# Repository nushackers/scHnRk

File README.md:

# scHnRk

The scHnRk (pronounced as snark) is a digispark/arduino compatible prototyping board developed for Hack&Roll'16.

The hardware design, firmware and software are derived from Galvant/usb_wrapper-pcb, digispark, micronucleus and arduino. Any derivative from their work is released under the Creative Commons License CC BY 4.0 wherever possible. (I'm no lawyer)

## Hardware

This design is adapted from the venerable DigiSpark.

Here's the lowdown on the stats
- ATTINY85
  - 8KB Flash Memory
  - 512B EEPROM
  - 6 I/O Pins (SPI)
- Acessories
  - 5 WS2812B LEDs
  - 2 CR2032 Battery Holders
  - 2 LEDs (Status, Pwr)
  - USB Wrapper (In some circles its called USB Condom)
  - USB Connector

The scHnRk consists of 2 independent components, separable from one another. The main componenet is a digispark clone which is fully assembled, the smaller component is a partially assembled/ unassembled usb-wrapper-pcb kit. 

## Kits

### Green (unassembled usb-wrapper-pcb)

- Resistor Information for green kits can be inferred from the following  
  - Galvant/usb_wrapper-pcb (Github)
    - Most basic configuration => R7 == 75K Ohm, R9 == 43.2K Ohm, R8 == R10 == 49.9K Ohm
    - R4 == 180 Ohm, LED == LED

### Orange (partially assembled usb-wrapper-pcb)

- Just solder on USB connector and you're set!

## Firmware

A jig will be provided on the day itself for firmware (bootloader) reprogramming using SPI. 

## Software

Feel free to program your arduino anyway you want during the competition using arduino IDE and the "on board" USB port!

## Designed by

```
NUSHackers and Pals

Chang Chu-Ming
Chinmay Pendharkar
Harish Venkatesan
Kenneth Lim
Vishnu Prem
Rahul Gokul
Sayanee Basu
Shanmugam Mpl
Yeo Kheng Meng
Jeremias Wong
```

## Secret Features

One has to be granted WOC REPUS Previleges before one accesses the secret features/puzzle.

There might be prizes for people who crack the puzzle during the hackathon! Maybe we forgot lol?

## Sponsors
 
### Platinum Sponsor
```
Zalora
```

### Gold Sponsors
```
Garena
Palantir
```

### Silver Sponsors
```
Titansoft
Google
Jane Street
Stripe
```

### Bronze Sponsors
```
Zopim
Carousell
NUS School of Computing
```

We thank the sponsors for making this happen.

Also we're looking out for sponsors for the next hackathon! Please contact us at coreteam@nushackers.org!

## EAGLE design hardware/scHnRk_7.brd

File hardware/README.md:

# Hardware

We highlight here the changes made between revisions

## v0.7

## v0.6

Converted to ATTINY85

## v0.1-v0.5

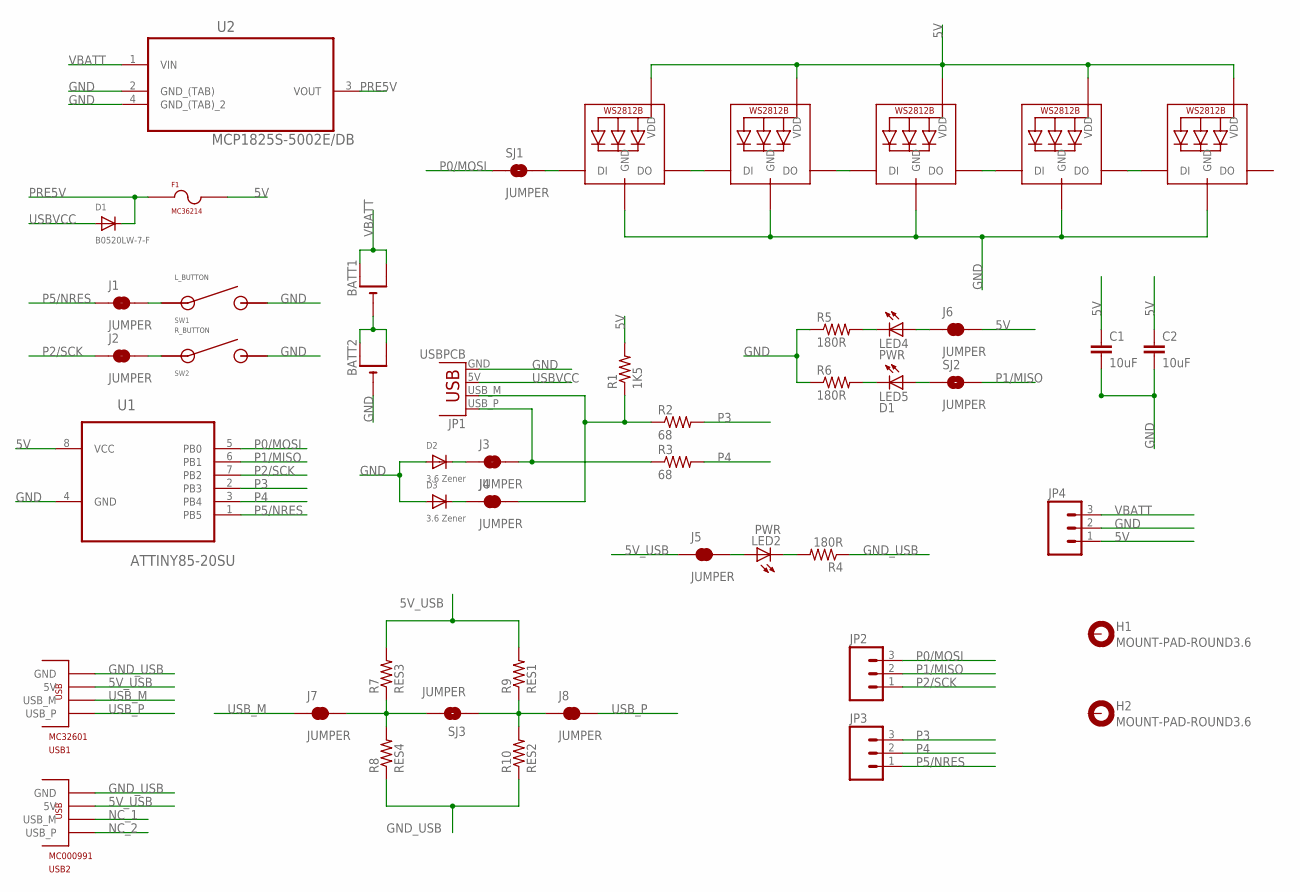
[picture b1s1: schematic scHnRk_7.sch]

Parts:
BATT1, BATT2: CR2032SMT; CR2032-SMD
C1, C2: 10uF; 0805
D1: B0520LW-7-F; SOD-123
D2, D3: 3.6 Zener; SOD-523
F1: MC36214
H1, H2: MOUNT-PAD-ROUND3.6; 3,6-PAD
J1, J2, J3, J4, J5, J6, J7, J8: JUMPER; PAD-JUMPER-2-NC_BY_TRACE_YES_SILK
JP1: USBPCB; USB-A-PCB
JP2, JP3, JP4: M031X03_NO_SILK; 1X03_NO_SILK
LED1, LED3, LED6, LED7, LED8: WS2812B5050; WS2812B
LED2, LED4: PWR; CHIPLED_0603
LED5: D1; CHIPLED_0603
R1: 1K5; 0805
R2, R3: 68; 0805
R4, R5, R6: 180R; 0805
R7: RES3; 0805
R8: RES4; 0805
R9: RES1; 0805
R10: RES2; 0805
SJ1, SJ2, SJ3: JUMPER; PAD-JUMPER-2-NO_YES_SILK
SW1: L_BUTTON; SKRBAGE010
SW2: R_BUTTON; SKRBAGE010
U1: ATTINY85-20SU; SOIC127P798X216-8N
U2: MCP1825S-5002E/DB; SOT230P700X180-4N
USB1: MC32601
USB2: MC000991

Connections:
5V: C1.1, C2.1, F1.P$2, J6.2, JP4.1, LED1.1-VDD (VDD), LED3.1-VDD (VDD), LED6.1-VDD (VDD), LED7.1-VDD (VDD), LED8.1-VDD (VDD), R1.2, U1.8 (VCC)
5V_USB: J5.1, R7.2, R9.2, USB1.P$2 (5V), USB2.P$4 (5V)
GND: BATT2.-, C1.2, C2.2, D2.A, D3.A, JP1.GND, JP4.2, LED1.3-GND (GND), LED3.3-GND (GND), LED6.3-GND (GND), LED7.3-GND (GND), LED8.3-GND (GND), R5.1, R6.1, SW1.P$2, SW1.P$4, SW2.P$2, SW2.P$4, U1.4 (GND), U2.2 (GND_(TAB)), U2.4 (GND_(TAB)_2)
GND_USB: R4.1, R8.1, R10.1, USB1.P$5 (GND), USB2.P$1 (GND)
unnamed: BATT1.-, BATT2.+$1 (+), BATT2.+$2 (+1)
unnamed: J1.2, SW1.P$1, SW1.P$3
unnamed: LED1.2-DOUT (DO), LED3.4-DIN (DI)
unnamed: LED3.2-DOUT (DO), LED6.4-DIN (DI)
unnamed: LED6.2-DOUT (DO), LED7.4-DIN (DI)
unnamed: LED7.2-DOUT (DO), LED8.4-DIN (DI)
unnamed: J5.2, LED2.A
unnamed: J2.2, SW2.P$1, SW2.P$3
unnamed: D2.K (C), J3.1
unnamed: D3.K (C), J4.1
unnamed: LED1.4-DIN (DI), SJ1.2
unnamed: J4.2, JP1.USB_M (D-), R1.1, R2.1
unnamed: J3.2, JP1.USB_P (D+), R3.1
unnamed: J7.2, R7.1, R8.2, SJ3.2
unnamed: J8.1, R9.1, R10.2, SJ3.1
unnamed: LED2.C, R4.2
unnamed: LED4.C, R5.2
unnamed: LED5.C, R6.2
unnamed: J6.1, LED4.A
unnamed: LED5.A, SJ2.1
NC_1: USB2.P$3 (USB_M)
NC_2: USB2.P$2 (USB_P)
P0/MOSI: JP2.3, SJ1.1, U1.5 (PB0)
P1/MISO: JP2.2, SJ2.2, U1.6 (PB1)
P2/SCK: J2.1, JP2.1, U1.7 (PB2)
P3: JP3.3, R2.2, U1.2 (PB3)
P4: JP3.2, R3.2, U1.3 (PB4)
P5/NRES: J1.1, JP3.1, U1.1 (PB5)
PRE5V: D1.C, F1.P$1, U2.3 (VOUT)
USBVCC: D1.A, JP1.5V (VBUS)
USB_M: J7.1, USB1.P$3 (USB_M)
USB_P: J8.2, USB1.P$4 (USB_P)
VBATT: BATT1.+$1 (+), BATT1.+$2 (+1), JP4.3, U2.1 (VIN)

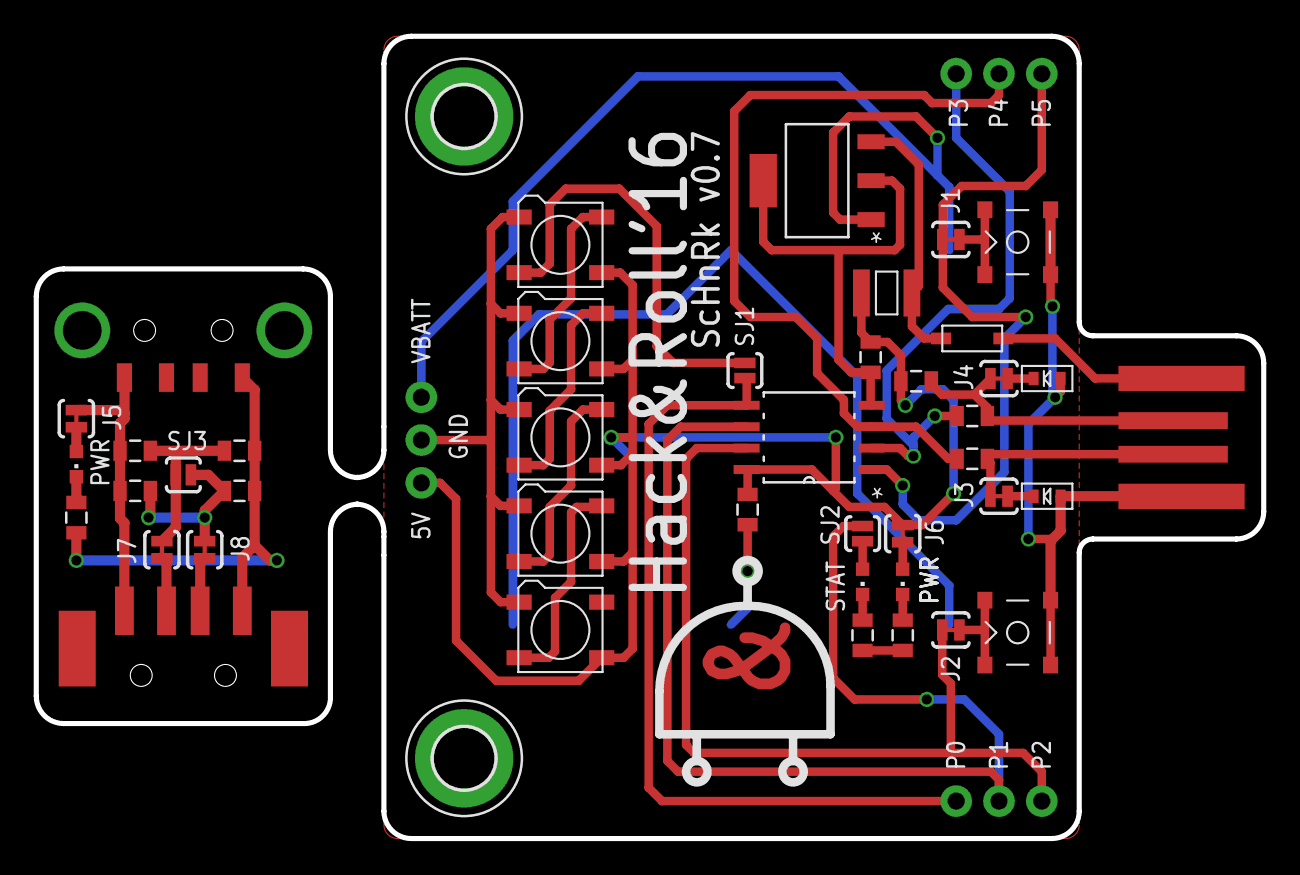
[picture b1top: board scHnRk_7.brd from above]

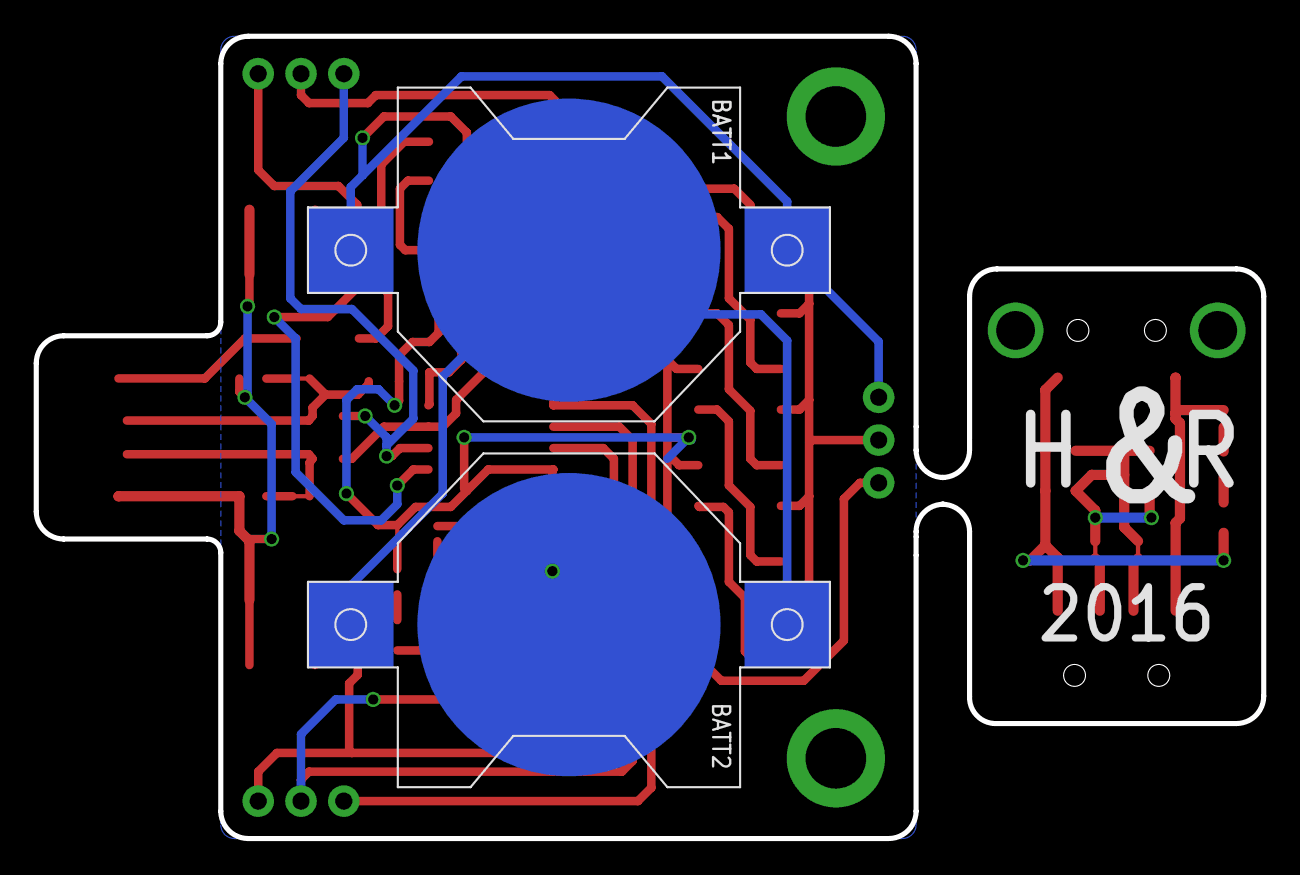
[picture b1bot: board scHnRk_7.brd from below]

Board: 2 copper layers, 72.9 x 47.6 mm, 49 parts (2 on the bottom side), 35 nets.

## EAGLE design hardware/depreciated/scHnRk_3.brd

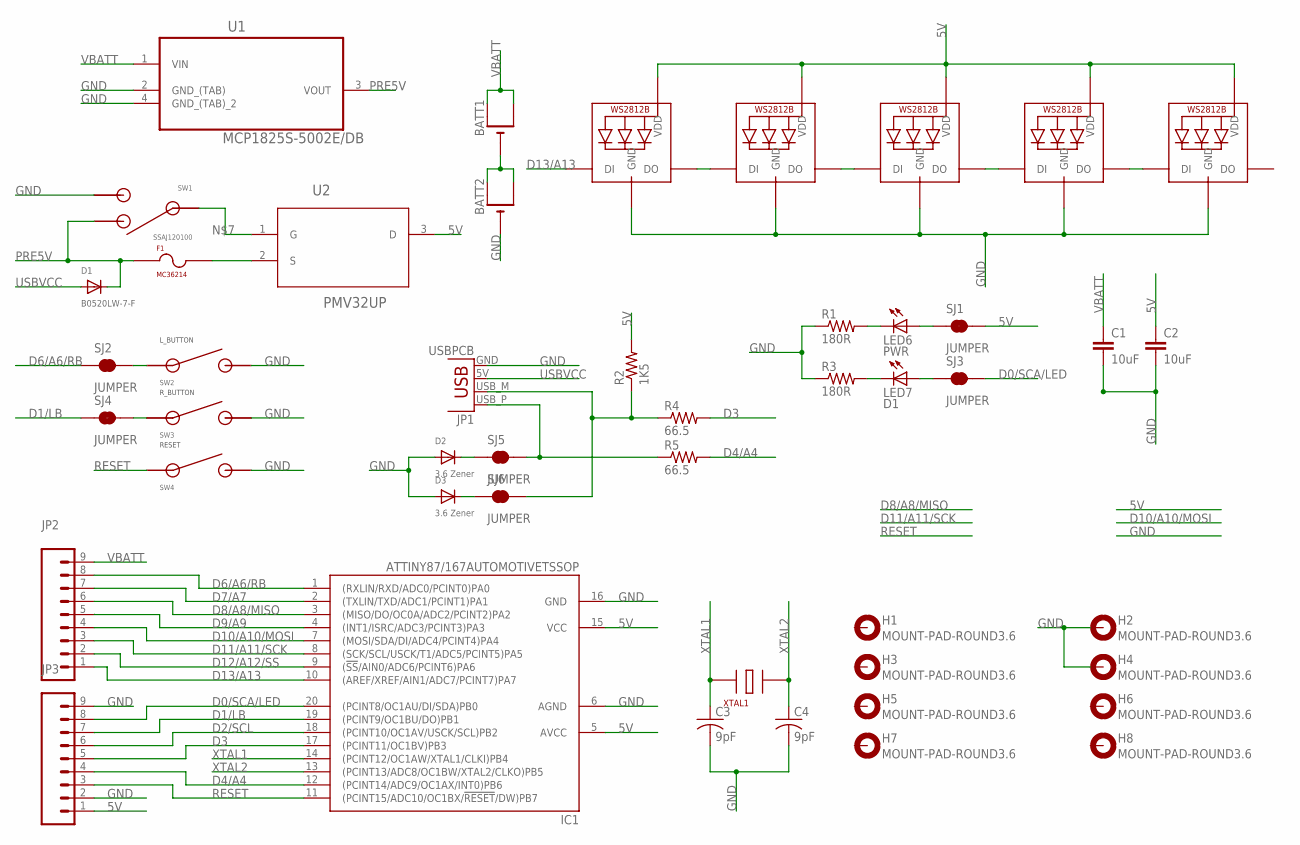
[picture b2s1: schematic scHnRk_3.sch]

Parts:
BATT1, BATT2: CR2032SMT; CR2032-SMD
C1, C2: 10uF; 0805
C3, C4: 9pF; C0603K
D1: B0520LW-7-F; SOD-123
D2, D3: 3.6 Zener; SOD-523
F1: MC36214
H1, H2, H3, H4, H5, H6, H7, H8: MOUNT-PAD-ROUND3.6; 3,6-PAD
IC1: ATTINY87/167AUTOMOTIVETSSOP; TSSOP20
JP1: USBPCB; USB-A-PCB
JP2, JP3: M09; 1X09
LED1, LED2, LED3, LED4, LED5: WS2812B5050; WS2812B
LED6: PWR; CHIPLED_0603
LED7: D1; CHIPLED_0603
R1, R3: 180R; R0603
R2: 1K5; R0603
R4, R5: 66.5; R0603
SJ1, SJ2, SJ3, SJ4, SJ5, SJ6: JUMPER; PAD-JUMPER-2-NC_BY_TRACE_YES_SILK
SW1: SSAJ120100
SW2: L_BUTTON; SKRBAGE010
SW3: R_BUTTON; SKRBAGE010
SW4: RESET; SKRBAGE010
U1: MCP1825S-5002E/DB; SOT230P700X180-4N
U2: PMV32UP; SOT95P230X110-3N
XTAL1: 16MHZ-2467444

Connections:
5V: C2.1, IC1.5 (AVCC), IC1.15 (VCC), JP3.1, LED1.1-VDD (VDD), LED2.1-VDD (VDD), LED3.1-VDD (VDD), LED4.1-VDD (VDD), LED5.1-VDD (VDD), R2.2, SJ1.2, U2.3 (D)
D0/SCA/LED: IC1.20 ((PCINT8/OC1AU/DI/SDA)PB0), JP3.8, SJ3.2
D1/LB: IC1.19 ((PCINT9/OC1BU/DO)PB1), JP3.7, SJ4.1
D2/SCL: IC1.18 ((PCINT10/OC1AV/USCK/SCL)PB2), JP3.6
D3: IC1.17 ((PCINT11/OC1BV)PB3), JP3.5, R4.2
D4/A4: IC1.12 ((PCINT14/ADC9/OC1AX/INT0)PB6), JP3.4, R5.2
D6/A6/RB: IC1.1 ((RXLIN/RXD/ADC0/PCINT0)PA0), JP2.8, SJ2.1
D7/A7: IC1.2 ((TXLIN/TXD/ADC1/PCINT1)PA1), JP2.7
D8/A8/MISO: IC1.3 ((MISO/DO/OC0A/ADC2/PCINT2)PA2), JP2.6
D9/A9: IC1.4 ((INT1/ISRC/ADC3/PCINT3)PA3), JP2.5
D10/A10/MOSI: IC1.7 ((MOSI/SDA/DI/ADC4/PCINT4)PA4), JP2.4
D11/A11/SCK: IC1.8 ((SCK/SCL/USCK/T1/ADC5/PCINT5)PA5), JP2.3
D12/A12/SS: IC1.9 ((!SS!/AIN0/ADC6/PCINT6)PA6), JP2.2
D13/A13: IC1.10 ((AREF/XREF/AIN1/ADC7/PCINT7)PA7), JP2.1, LED1.4-DIN (DI)
GND: BATT2.-, C1.2, C2.2, C3.2, C4.2, D2.A, D3.A, H2.B3,6, H4.B3,6, IC1.6 (AGND), IC1.16 (GND), JP1.GND, JP3.2, JP3.9, LED1.3-GND (GND), LED2.3-GND (GND), LED3.3-GND (GND), LED4.3-GND (GND), LED5.3-GND (GND), R1.1, R3.1, SW1.P$2, SW2.P$2, SW2.P$4, SW3.P$2, SW3.P$4, SW4.P$2, SW4.P$4, U1.2 (GND_(TAB)), U1.4 (GND_(TAB)_2)
unnamed: BATT1.-, BATT2.+$1 (+), BATT2.+$2 (+1)
unnamed: SJ2.2, SW2.P$1, SW2.P$3
unnamed: LED1.2-DOUT (DO), LED2.4-DIN (DI)
unnamed: LED2.2-DOUT (DO), LED3.4-DIN (DI)
unnamed: LED3.2-DOUT (DO), LED4.4-DIN (DI)
unnamed: LED4.2-DOUT (DO), LED5.4-DIN (DI)
unnamed: SW1.P$C, U2.1 (G)
unnamed: SJ4.2, SW3.P$1, SW3.P$3
unnamed: D2.K (C), SJ5.1
unnamed: D3.K (C), SJ6.1
unnamed: JP1.USB_M (D-), R2.1, R4.1, SJ6.2
unnamed: JP1.USB_P (D+), R5.1, SJ5.2
unnamed: F1.P$2, U2.2 (S)
unnamed: LED6.C, R1.2
unnamed: LED7.C, R3.2
unnamed: LED6.A, SJ1.1
unnamed: LED7.A, SJ3.1
PRE5V: D1.C, F1.P$1, SW1.P$1, U1.3 (VOUT)
RESET: IC1.11 ((PCINT15/ADC10/OC1BX/!RESET!/DW)PB7), JP3.3, SW4.P$1, SW4.P$3
USBVCC: D1.A, JP1.5V (VBUS)
VBATT: BATT1.+$1 (+), BATT1.+$2 (+1), C1.1, JP2.9, U1.1 (VIN)
XTAL1: C3.1, IC1.14 ((PCINT12/OC1AW/XTAL1/CLKI)PB4), XTAL1.P$1
XTAL2: C4.1, IC1.13 ((PCINT13/ADC8/OC1BW/XTAL2/CLKO)PB5), XTAL1.P$3

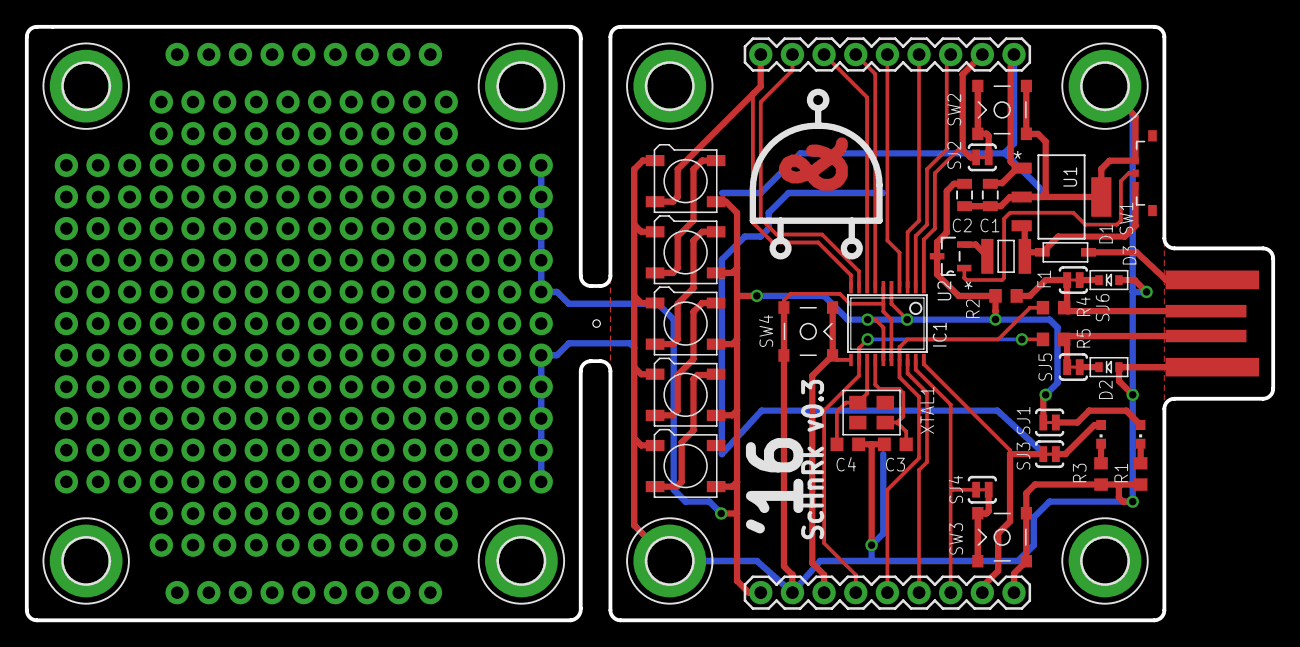
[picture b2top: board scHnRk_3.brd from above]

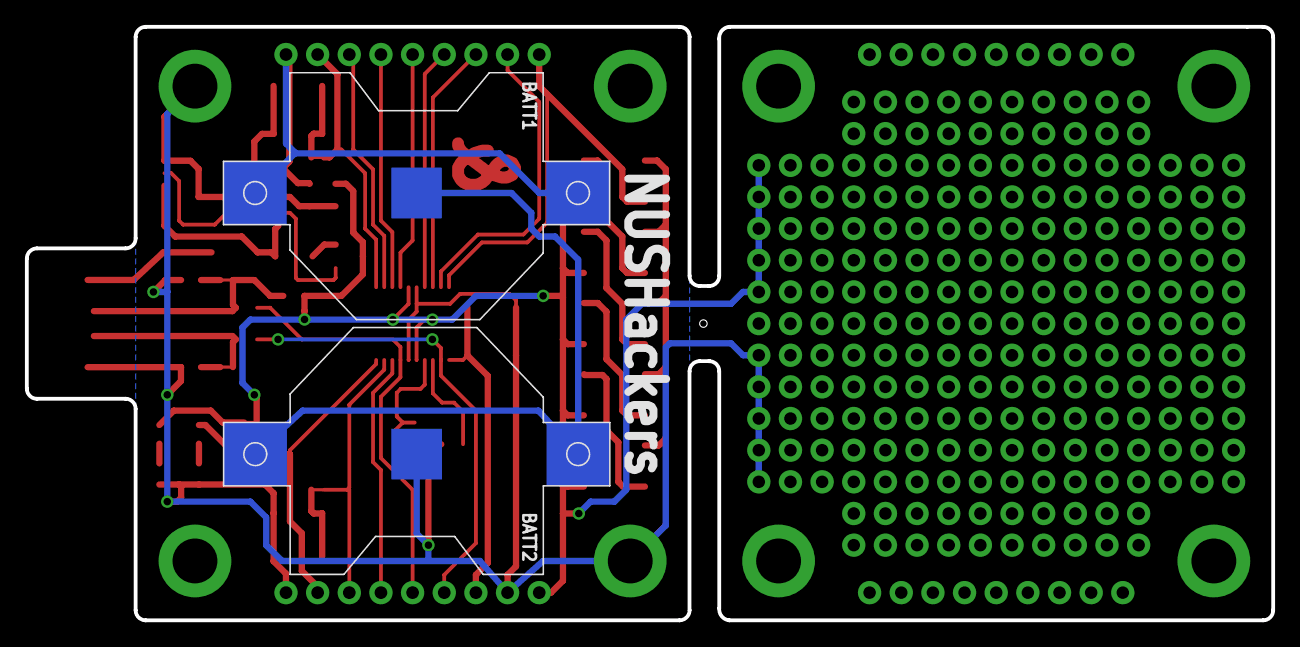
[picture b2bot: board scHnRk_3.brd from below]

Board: 2 copper layers, 100.0 x 47.6 mm, 47 parts (2 on the bottom side), 38 nets.

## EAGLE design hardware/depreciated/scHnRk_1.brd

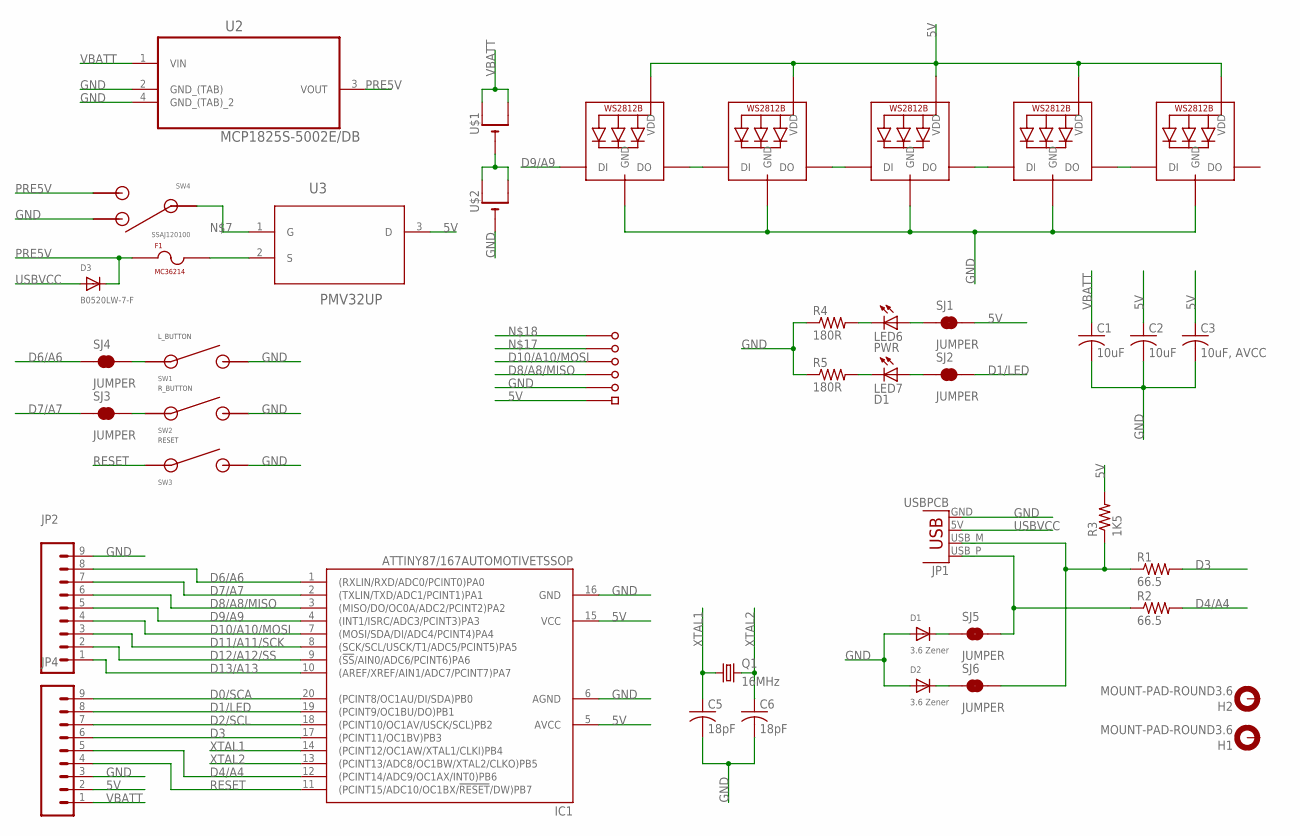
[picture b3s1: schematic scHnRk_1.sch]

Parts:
C1, C2: 10uF; C1206K
C3: 10uF, AVCC; C1206K
C5, C6: 18pF; C0603K
D1, D2: 3.6 Zener; SOD-523
D3: B0520LW-7-F; SOD-123
F1: MC36214
H1, H2: MOUNT-PAD-ROUND3.6; 3,6-PAD
IC1: ATTINY87/167AUTOMOTIVETSSOP; TSSOP20
JP1: USBPCB; USB-A-PCB
JP2, JP4: M09; 1X09
LED1, LED2, LED3, LED4, LED5: WS2812B5050; WS2812B
LED6: PWR; CHIPLED_0603
LED7: D1; CHIPLED_0603
Q1: 16MHz; HC49UP
R1, R2: 66.5; R0603
R3: 1K5; R0603
R4, R5: 180R; R0603
SJ1, SJ2, SJ3, SJ4, SJ5, SJ6: JUMPER; PAD-JUMPER-2-NC_BY_TRACE_YES_SILK
SW1: L_BUTTON; SKRBAGE010
SW2: R_BUTTON; SKRBAGE010
SW3: RESET; SKRBAGE010
SW4: SSAJ120100
TP1, TP3, TP4, TP5, TP6: TP-R
TP2: TP-S; TP_S
U2: MCP1825S-5002E/DB; SOT230P700X180-4N
U3: PMV32UP; SOT95P230X110-3N
U$1, U$2: CR2032SMT; CR2032-SMD

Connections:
5V: C2.1, C3.1, IC1.5 (AVCC), IC1.15 (VCC), JP4.2, LED1.1-VDD (VDD), LED2.1-VDD (VDD), LED3.1-VDD (VDD), LED4.1-VDD (VDD), LED5.1-VDD (VDD), R3.2, SJ1.2, TP2.P$1, U3.3 (D)
D0/SCA: IC1.20 ((PCINT8/OC1AU/DI/SDA)PB0), JP4.9
D1/LED: IC1.19 ((PCINT9/OC1BU/DO)PB1), JP4.8, SJ2.2
D2/SCL: IC1.18 ((PCINT10/OC1AV/USCK/SCL)PB2), JP4.7
D3: IC1.17 ((PCINT11/OC1BV)PB3), JP4.6, R1.2
D4/A4: IC1.12 ((PCINT14/ADC9/OC1AX/INT0)PB6), JP4.5, R2.2
D6/A6: IC1.1 ((RXLIN/RXD/ADC0/PCINT0)PA0), JP2.8, SJ4.1
D7/A7: IC1.2 ((TXLIN/TXD/ADC1/PCINT1)PA1), JP2.7, SJ3.1
D8/A8/MISO: IC1.3 ((MISO/DO/OC0A/ADC2/PCINT2)PA2), JP2.6, TP3.P$1
D9/A9: IC1.4 ((INT1/ISRC/ADC3/PCINT3)PA3), JP2.5, LED1.4-DIN (DI)
D10/A10/MOSI: IC1.7 ((MOSI/SDA/DI/ADC4/PCINT4)PA4), JP2.4, TP4.P$1
D11/A11/SCK: IC1.8 ((SCK/SCL/USCK/T1/ADC5/PCINT5)PA5), JP2.3
D12/A12/SS: IC1.9 ((!SS!/AIN0/ADC6/PCINT6)PA6), JP2.2
D13/A13: IC1.10 ((AREF/XREF/AIN1/ADC7/PCINT7)PA7), JP2.1
GND: C1.2, C2.2, C3.2, C5.2, C6.2, D1.A, D2.A, IC1.6 (AGND), IC1.16 (GND), JP1.GND, JP2.9, JP4.3, LED1.3-GND (GND), LED2.3-GND (GND), LED3.3-GND (GND), LED4.3-GND (GND), LED5.3-GND (GND), R4.1, R5.1, SW1.P$2, SW1.P$4, SW2.P$2, SW2.P$4, SW3.P$2, SW3.P$4, SW4.P$1, TP1.P$1, U2.2 (GND_(TAB)), U2.4 (GND_(TAB)_2), U$2.-
unnamed: U$1.-, U$2.+$1 (+), U$2.+$2 (+1)
unnamed: SJ4.2, SW1.P$1, SW1.P$3
unnamed: LED1.2-DOUT (DO), LED2.4-DIN (DI)
unnamed: LED2.2-DOUT (DO), LED3.4-DIN (DI)
unnamed: LED3.2-DOUT (DO), LED4.4-DIN (DI)
unnamed: LED4.2-DOUT (DO), LED5.4-DIN (DI)
unnamed: SW4.P$C, U3.1 (G)
unnamed: SJ3.2, SW2.P$1, SW2.P$3
unnamed: D1.K (C), SJ5.1
unnamed: D2.K (C), SJ6.1
unnamed: JP1.USB_M (D-), R1.1, R3.1, SJ6.2
unnamed: JP1.USB_P (D+), R2.1, SJ5.2
unnamed: F1.P$2, U3.2 (S)
unnamed: LED6.C, R4.2
unnamed: LED7.C, R5.2
unnamed: LED6.A, SJ1.1
unnamed: LED7.A, SJ2.1
PRE5V: D3.C, F1.P$1, SW4.P$2, U2.3 (VOUT)
RESET: IC1.11 ((PCINT15/ADC10/OC1BX/!RESET!/DW)PB7), JP4.4, SW3.P$1, SW3.P$3
USBVCC: D3.A, JP1.5V (VBUS)
VBATT: C1.1, JP4.1, U2.1 (VIN), U$1.+$1 (+), U$1.+$2 (+1)
XTAL1: C5.1, IC1.14 ((PCINT12/OC1AW/XTAL1/CLKI)PB4), Q1.1
XTAL2: C6.1, IC1.13 ((PCINT13/ADC8/OC1BW/XTAL2/CLKO)PB5), Q1.2

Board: 2 copper layers, 48 parts (2 on the bottom side), 38 nets, no tracks yet.

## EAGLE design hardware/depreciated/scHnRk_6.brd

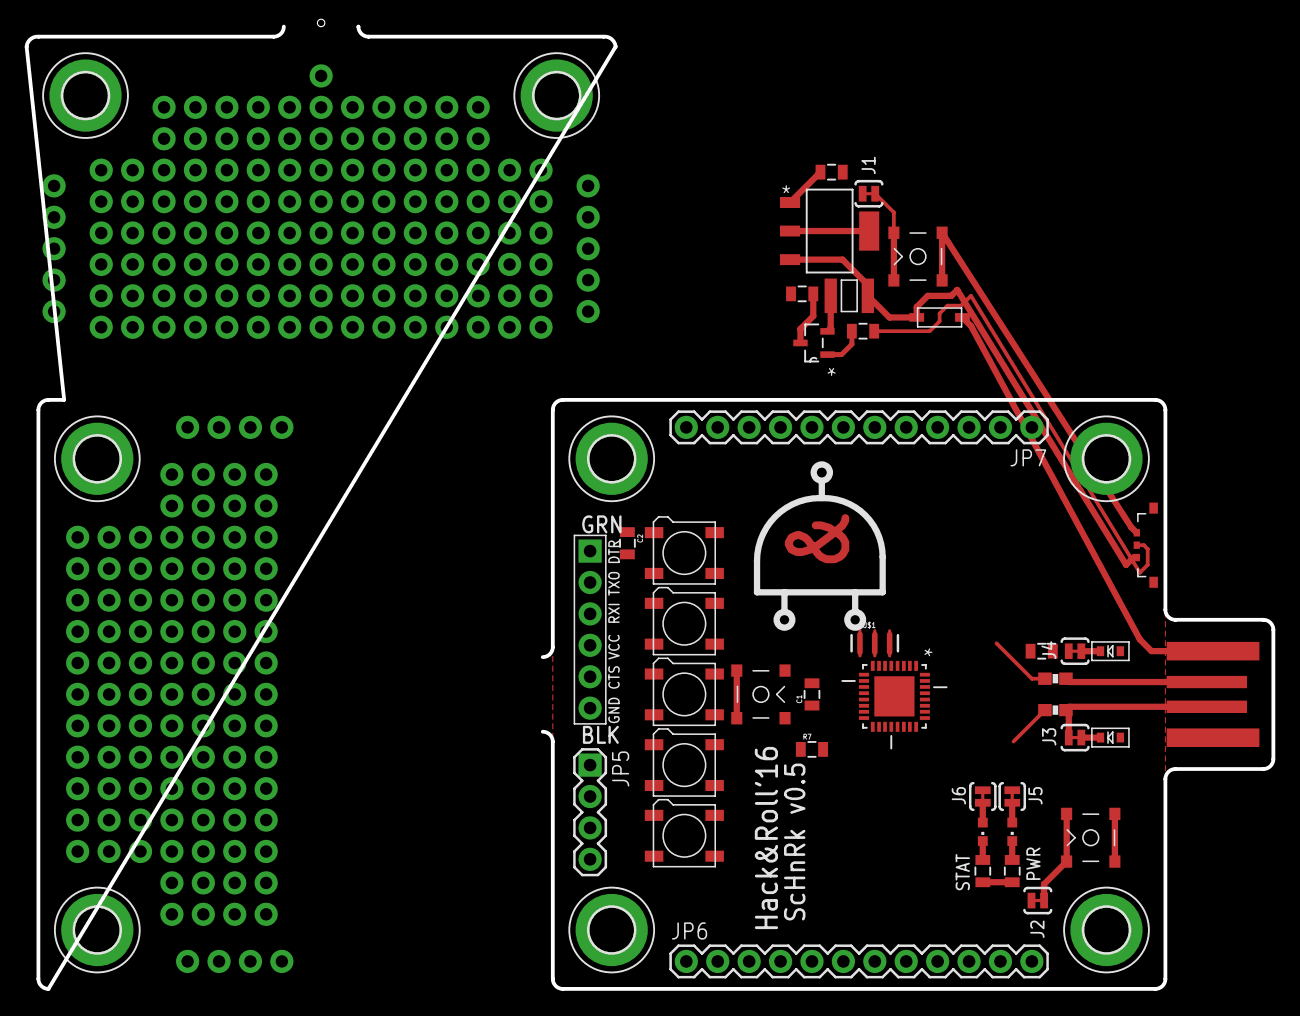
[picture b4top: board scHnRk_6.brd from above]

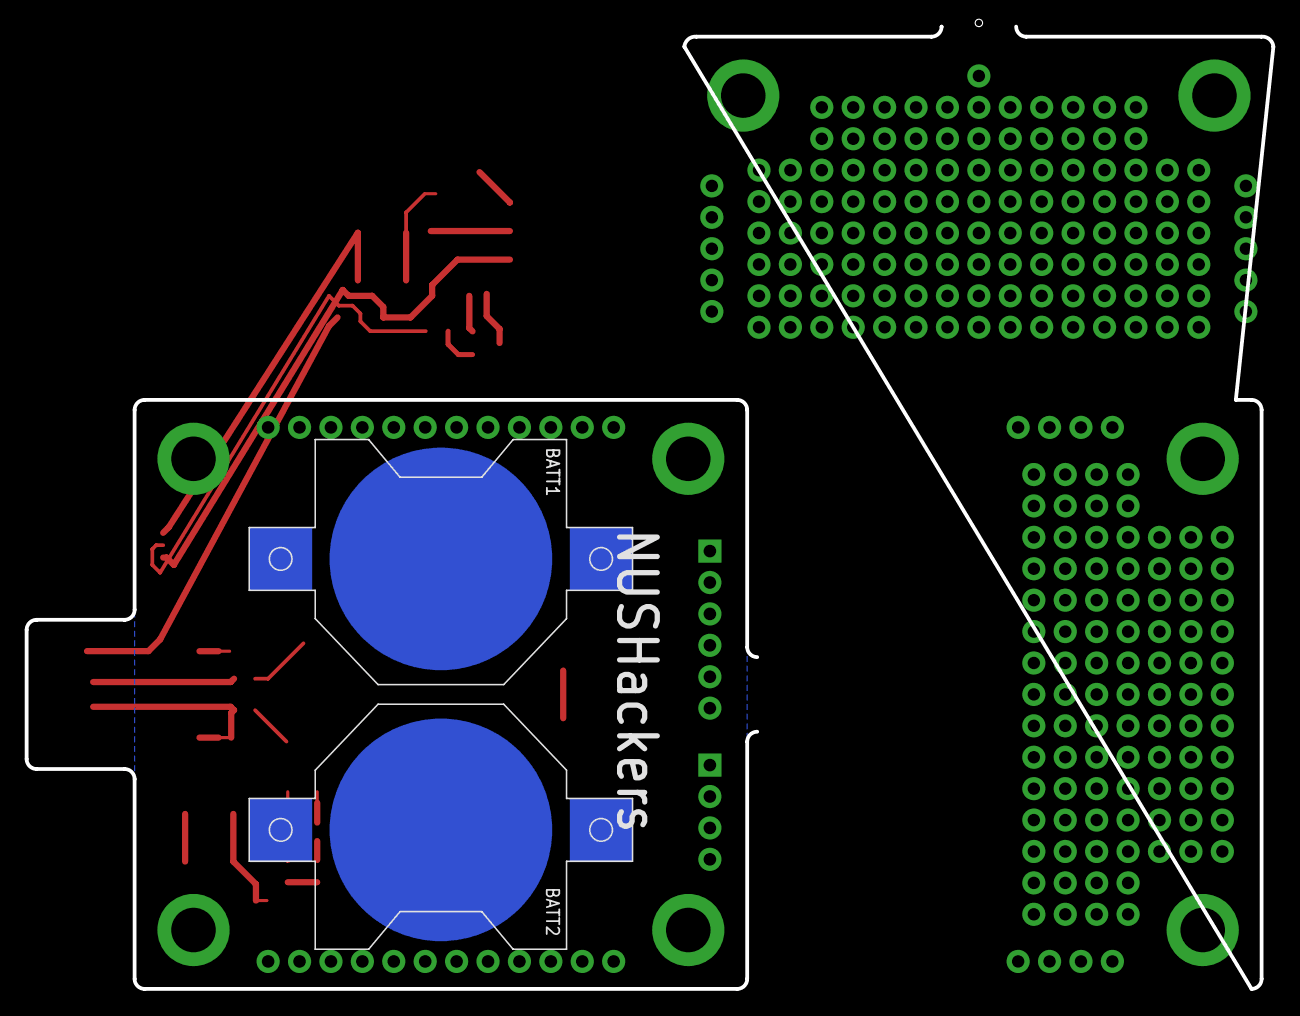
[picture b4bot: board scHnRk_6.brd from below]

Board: 2 copper layers, 100.8 x 77.8 mm, 51 parts (2 on the bottom side), 40 nets.

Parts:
BATT1, BATT2: CR2032-SMD
C1, C2: 0.1uF; 0805
C3, C4: 10uF; 0805
D1: B0520LW-7-F; SOD-123
D2, D3: 3.6 Zener; SOD-523
F1: MC36214
H1, H2, H3, H4, H5, H6, H7, H8: MOUNT-PAD-ROUND3.6; 3,6-PAD
J1, J2, J3, J4, J5, J6: JUMPER; PAD-JUMPER-2-NC_BY_TRACE_YES_SILK
JP3: USBPCB; USB-A-PCB
JP4: FTDI_DEVICE; FTDI_DEVICE_SIDE
JP5: 1X04
JP6, JP7: 1X12
LED1, LED2, LED5, LED6, LED7: WS2812B5050; WS2812B
LED3: PWR; CHIPLED_0603
LED4: D1; CHIPLED_0603
R1, R6: 1K5; 0805
R2, R3: 66.5; 0603-RES
R4, R5: 180R; 0805
R7: 10k; 0805
SW1: SSAJ120100
SW2: L_BUTTON; SKRBAGE010
SW3: R_BUTTON; SKRBAGE010
SW4: RESET; SKRBAGE010
U1: MCP1825S-5002E/DB; SOT230P700X180-4N
U2: PMV32UP; SOT95P230X110-3N
U4: ATMEGA328P-MU; QFN50P500X500X100-33N
U$1: 16MHZ; RESONATOR-SMD

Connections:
5V: C4.1, J5.2, JP4.P$4, JP5.2, LED1.1-VDD, LED2.1-VDD, LED5.1-VDD, LED6.1-VDD, LED7.1-VDD, R1.2, R7.1, U2.3, U4.4, U4.6, U4.18
A4/SDA: JP5.3, U4.27
A5/SCL: JP5.4, U4.28
D0/RXD: JP4.P$2, JP7.1, U4.30
D1/TXD: JP4.P$3, JP7.2, U4.31
D2: R3.2, U4.32
D3: JP7.3, U4.1
D4: JP7.4, U4.2
D5: JP7.5, U4.9
D6: JP7.6, U4.10
D7: R2.2, U4.11
D8: JP7.7, U4.12
D13/SCK: J6.2, U4.17
GND: BATT2.-, C1.1, C3.2, C4.2, D2.A, D3.A, JP3.GND, JP4.P$5, JP4.P$6, JP5.1, LED1.3-GND, LED2.3-GND, LED5.3-GND, LED6.3-GND, LED7.3-GND, R4.1, R5.1, SW1.P$2, SW2.P$2, SW2.P$4, SW3.P$2, SW3.P$4, SW4.P$2, SW4.P$4, U1.2, U1.4, U4.3, U4.5, U4.21, U$1.2
unnamed: BATT1.-, BATT2.+$1, BATT2.+$2
unnamed: J1.2, SW2.P$1, SW2.P$3
unnamed: LED1.2-DOUT, LED2.4-DIN
unnamed: LED2.2-DOUT, LED5.4-DIN
unnamed: LED5.2-DOUT, LED6.4-DIN
unnamed: LED6.2-DOUT, LED7.4-DIN
unnamed: R6.2, SW1.P$C
unnamed: J2.2, SW3.P$1, SW3.P$3
unnamed: D2.K, J3.1
unnamed: D3.K, J4.1
unnamed: J4.2, JP3.USB_M, R1.1, R2.1
unnamed: J3.2, JP3.USB_P, R3.1
unnamed: R6.1, U2.1
unnamed: F1.P$2, U2.2
unnamed: C2.2, JP4.P$1
unnamed: LED3.C, R4.2
unnamed: LED4.C, R5.2
unnamed: J5.1, LED3.A
unnamed: J6.1, LED4.A
unnamed: C1.2, U4.20
PRE5V: D1.C, F1.P$1, SW1.P$1, U1.3
RESET: C2.1, R7.2, SW4.P$1, SW4.P$3, U4.29
USBVCC: D1.A, JP3.5V
VBATT: BATT1.+$1, BATT1.+$2, C3.1, U1.1
XTAL1: U4.7, U$1.3
XTAL2: U4.8, U$1.1

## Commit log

2015-12-10 Init Commit
2015-12-11 schnrk v0.2
2015-12-11 updated helpers
2015-12-11 added some vague help text
2015-12-14 edited gitignore
2015-12-14 added new revisions
2015-12-15 updated to version 5, starting on version 6, moved buttons to edge, add resistor to gate of pwr mosfet
2015-12-17 added skeletons, transiting to atmega328p-mu
2016-01-06 updated board, sent to board house
2016-01-06 just added neopixel prog
2016-01-06 updated readmes to reflect changes
2016-01-06 whoops, minor edit
2016-01-18 added base firmware
2016-01-19 added pdfs
2016-01-23 added more info

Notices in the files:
parts and their libraries:
SparkFun-Connectors: Licensing: Creative Commons ShareAlike 4.0 International - https://creativecommons.org/licenses/by-sa/4.0
